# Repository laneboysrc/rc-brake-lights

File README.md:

# RC Brake & Reversing Light controller

This project is an easy-to-build light controller for Radio Controlled cars that simulates realistic brake and reversing lights.

It hooks between your ESC and receiver.

The brake lights automatically turn on for a short, random time when the throttle goes to neutral. The reversing lights turn on when driving backwards.

The light controller supports various ESC modes to ensure the lights are in sync with the way your ESC controls the drive motor.

The aim of the project is to make it easy to build anyone with minimal electronics knowledge. **If you are unable to build it yourself please contact [laneboysrc@gmail.com](mailto:laneboysrc@gmail.com); we'd be happy to sell you one.**

If you are looking for more than just brake lights check out our full-featured [DIY RC Light Controller](https://github.com/laneboysrc/rc-light-controller).

## Building the electronics

The core of the light controller is the inexpensive STC STC15W104. It is a modern interpretation of the venerable 8051 MCU. This MCU was chosen due to its very low cost and because it can be programmed with an inexpensive USB-to-serial adapter, or using the serial port on a Raspberry Pi.

You can find the STC15W104 usually on eBay, AliExpress, Electrodragon, LCSC ...

Beside the MCU you need 3 resistors, a diode and a capacitor. The complete [list of components](electronics/BOM%20-%20Bill%20of%20Materials.txt) can be found in the `electronics/` folder

For convenience the [schematics are available as PDF file](electronics/rc-brake-lights-schematics.pdf).

Due to the small number of required components, the light controller can be easily built on a perfboard. The following image shows how to wire everything up:

(The [Fritzing](http://fritzing.org) source file for this drawing is provided in the `fritzing/` folder)

If you plan to build several controllers it may be worth-while to order printed circuit boards. [Gerber files](gerber-rc-brake-lights.zip) for manufacturing PCBS are provided, as well as the [KiCad source files](electronics/). Note that the PCB uses SMD components rather than through-hole. Still, it is designed for hand-soldering.

## Loading the firmware

You can find the pre-compiled firmware released as part of the project.

If you want to build or modify the firmware you will need [SDCC](http://sdcc.sourceforge.net) and [GNU Make](https://www.gnu.org/software/make/).

To flash the firmware into the STC15W104, use [STCGAL](https://github.com/grigorig/stcgal).

### Loading the firmware with an USB-to-serial adapter

Follow the instructions at [https://github.com/grigorig/stcgal#installation](https://github.com/grigorig/stcgal#installation) to install STCGAL. This programming tool for the STC MCU requires [Python 3](https://www.python.org/downloads/), and the Python 3 libraries `pyserial` and `tqdm`.

- Go to https://www.python.org and download Python; install it.
- Open a Command prompt (run cmd.exe)
- In the command prompt execute `pip install pyserial tqdm`

Connect your USB-to-serial adapter to the RC-brake-lights controller as follows:

Do not connect `+` yet, only after starting STCGAL.

Download the [firmware Intel-HEX file](rc-brake-lights.ihx) and execute STCGAL as follows:

    python stcgal.py -t 12000 --option low_voltage_reset=true --option low_voltage_threshold=0 --option eeprom_lvd_inhibit=true -b 1200 -p COM7 rc-brake-lights.ihx

*Important*: Replace the COM port number with the one of your USB-to-serial adapter. In Windows consult the Device Manager to find out which port number to use.

Once started, STCGAL prompts you to power-cycle the circuit. Plug in `+` and STCGAL should find the MCU and program it. Your controller is now ready to use.

### Loading the firmware using a Raspberry Pi

The Raspberry Pi has a serial port accessible on its GPIO pin-header, so we can use it directly for programming.

Connect the RC-brake-lights controller as follows:

Do not connect `+` yet, only after starting STCGAL.

Download and unpack STCGAL:

    wget https://github.com/grigorig/stcgal/archive/master.zip
    unzip master.zip

Install the required Python 3 modules:

    sudo apt install python3-serial python3-tqdm

Use `sudo raspi-config` and go to `Interface Options`, then `P6 Serial` where you can disable log-in via the serial console, and enable the serial hardware:

    Would you like a login shell to be accessible over serial? Select NO
    Would you like the serial port hardware to be enabled? Select YES

After rebooting, download the [firmware Intel-HEX file](rc-brake-lights.ihx) and execute STCGAL as follows:

    python3 stcgal-master/stcgal.py -p /dev/ttyAMA0 -t 12000 --option low_voltage_reset=true --option low_voltage_threshold=0 --option eeprom_lvd_inhibit=true -b 1200 rc-brake-lights.ihx

Once started, STCGAL prompts you to power-cycle the MCU. Plug in `+` and STCGAL should find the MCU and program it. Your controller is now ready to use.

## Connecting the light controller to your RC system

The light controller has two parallel connectors on the input side. Connect your ESC to one of the plugs and connect the TH input of the receiver with a male-to-male servo cable  to the other plug.

The `B` output drives two red LEDs in parallel for the brake light function, the `R` output drives two white LEDs in parallel for the reversing light function.

## Forward/Reverse setup

Depending on your RC system, out of the box the light controller may operate in the wrong direction (forward and backward reversed). To change this, press and hold the setup button on the light controller for 3 seconds. The LEDs will start flashing quickly.

Now move the throttle on the transmitter to the driving direction that would make the car move `forward`. When LEDs will go out and the light controller has now learned the correct direction of the throttle signal for `forward`. This setting is preserved, so you only have to do this once.

## Changing the ESC mode

When it comes to brake function, ESC models behave differently. The light controller can be programmed for the specific behavior of your ESC.

To change the ESC mode, perform the following steps:
Press and hold the setup button on the light controller. After 3 seconds, the LEDs will start to flash quickly. Press the setup button one more time. The light controller enters the ESC mode setting and flashes the current ESC mode number:

##### 1 flash: Forward/Brake/Reverse with timeout
When driving forward and then immediately pushing the throttle to reverse, the ESC performs a brake function. The ESC only allows driving backwards if the ESC has remained in neutral position for a few seconds.

Example: The China 320A ESC, HPI SC-15WP

##### 2 flashes: Forward/Brake/Reverse
After going forward and then into reverse, the ESC always performs the brake function -- even if the throttle remained in neutral for a long time.

Example: Tamiya ESCs

##### 3 flashes: Forward/Reverse (Crawler mode)
Crawler ESC with drag brake, where the ESC switches from forward directly
into reverse.

##### 4 flashes: Forward/Brake
ESC in race mode where reversing is not allowed.

Press the setup button repeatedly until the desired ESC mode has been selected. Then press-and hold the setup button until the LEDs stop flashing. The ESC mode has now been persistently stored.

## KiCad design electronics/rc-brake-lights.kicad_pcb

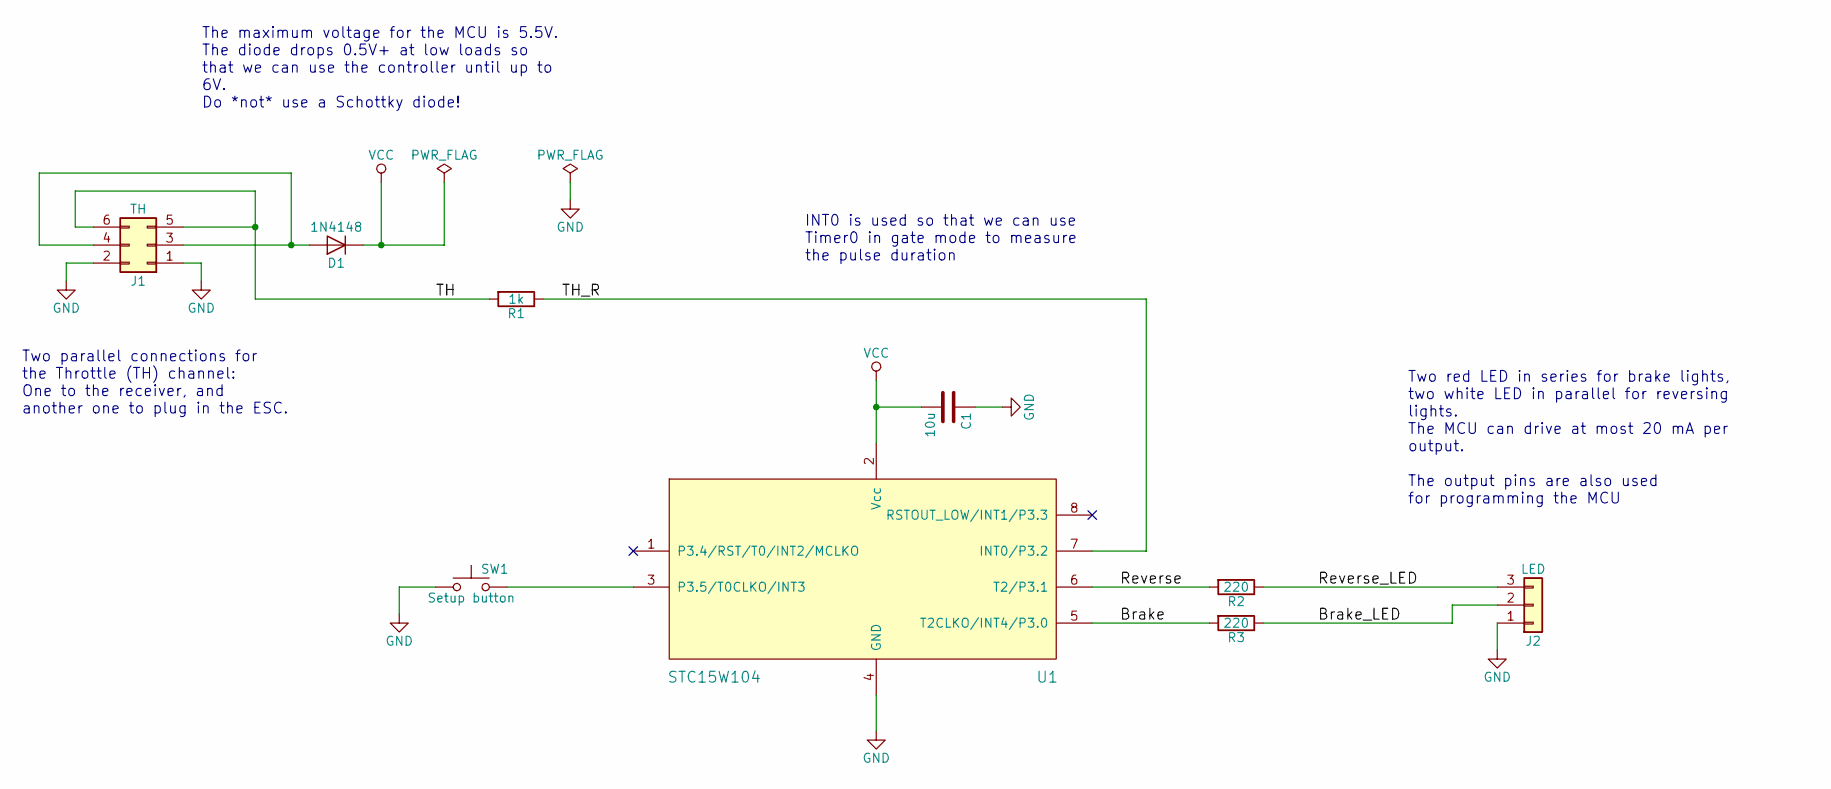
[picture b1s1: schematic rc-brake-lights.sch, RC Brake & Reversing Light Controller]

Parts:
C1: 10u; C_0603_HandSoldering
D1: 1N4148; D_SOD-323_HandSoldering
J1: TH; Pin_header_02x03_board_edge
J2: LED; Pin_Header_Angled_1x03_Pitch2.54mm
R1: 1k; R_0603_HandSoldering
R2, R3: 220; R_0603_HandSoldering
SW1: Setup button; Tact_switch_SMD_6x3_6x2_5
U1: STC15W104; SOIC-8-N

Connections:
/Brake: R3.2, U1.5 (T2CLKO/INT4/P3.0)
/Brake_LED: J2.2, R3.1
/Reverse: R2.2, U1.6 (T2/P3.1)
/Reverse_LED: J2.3, R2.1
/TH: J1.5, J1.6, R1.2
/TH_R: R1.1, U1.7 (INT0/P3.2)
GND: C1.1, J1.1, J1.2, J2.1, SW1.1, U1.4 (GND)
unnamed: D1.2 (A), J1.3, J1.4
unnamed: SW1.2, U1.3 (P3.5/T0CLKO/INT3)
VCC: C1.2, D1.1 (K), U1.2 (Vcc)

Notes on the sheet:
Two parallel connections for the Throttle (TH) channel: One to the receiver, and another one to plug in the ESC.
Two red LED in series for brake lights, two white LED in parallel for reversing lights. The MCU can drive at most 20 mA per output. The output pins are also used for programming the MCU
The maximum voltage for the MCU is 5.5V. The diode drops 0.5V+ at low loads so that we can use the controller until up to 6V. Do *not* use a Schottky diode!
INT0 is used so that we can use Timer0 in gate mode to measure the pulse duration

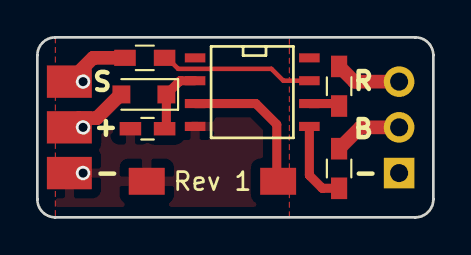
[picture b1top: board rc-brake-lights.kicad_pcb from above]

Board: 2 copper layers, 22.0 x 10.0 mm, 9 parts (1 on the bottom side), 10 nets.

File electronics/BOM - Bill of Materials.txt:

Partlist for the RC Brake & Reversing Light Controller


Perfboard version with through-hole components
----------------------------------------------

Part  Value      Device            Package           Description
C1    10uF/10V   C-Pol             Radial            Electrolytic capacitor, exact value not important
D1    1N4148     D                 Throughole        Signal diode, must be an ordinary silicon diode, not a Schottky diode
J1               Pin-header        2x3               Pin header for throttle servo input
J2               Pin-header        1x3               Pin header for LED output
R1    1k         R                 Throughhole       Resistor 1/8W or more
R2    220        R                 Throughhole       Resistor 1/8W or more
R2    220        R                 Throughhole       Resistor 1/8W or more
U1    STC15W104  MCU               DIP8              STC Microcontroller, 8051-based, 2.5..5.5V supply range
SW1              SPST                                Push button


PCB version with SMD components
-------------------------------

Part  Value      Device            Package           Description
C1    10uF/10V   C0603             0603              MLCC capacitor X7R or X5R
D1    T4         D                 SOD-123           Signal diode marked T4 (eBay, AliExpress)
J1               Pin-header        2x3               Pin header for throttle servo input
J2               Pin-header        1x3               Pin header for LED output
R1    1k         R                 0603              Resistor
R2    220        R                 0603              Resistor
R2    220        R                 0603              Resistor
U1    STC15W104  MCU               SOP8              STC Microcontroller, 8051-based, 2.5..5.5V supply range
SW1              SPST              3x6x2.5mm         Push button, e.g. https://www.aliexpress.com/item/100pcs-3X6X2-5mm-Tactile-Pus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

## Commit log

2018-03-27 PCB draft
2018-03-28 Add firmware skeleton and sublime project
2018-03-29 Add skeleton for modules
2018-04-01 Move IO pins so we can use T0 to measure pulse width
2018-04-01 Add MIT license
2018-04-01 Basic brake/reverse functionality implemented
2018-04-01 Add setup button
2018-04-01 Remove constant if statements
2018-04-02 Remove utils.h, introduce setup mode (replaces channel reversing)
2018-04-02 Implement setup mode and add overall code improvements
2018-04-02 Round-off the PCB edge
2018-04-02 Code cleanup
2018-04-02 Fix ESC mode description
2018-04-03 Make output connector right-angle
2018-04-04 Add low voltage reset
2018-04-04 Remove BOM file
2018-04-04 Add schematics and Gerbers sent for manufactoring
2018-04-04 Fix filename spelling
2018-04-04 Add Fritzing file
2018-04-05 Add BOM and breadboard drawing
2018-04-05 Add wiring diagram
2018-04-06 Add readme
2018-04-06 Update wiring diagram with ESC
2018-04-15 Set low power threshold for STC15W104
    Before we were using settings for STC15F104
2018-04-15 Add pre-compiled hex file
2018-04-15 Fix email link
2018-04-19 Improve documentation
2018-04-20 Add diagram how to connect to Raspi for flashing
2018-04-22 Add documentation for Raspi flashing after testing it
2018-05-04 Improve documentation of installation, add 3D impage
2018-06-02 Fix serial -> pyserial
2018-06-02 Fix spelling in python link
2018-06-02 Change command line to call python script
2018-06-02 Add port to command line
2022-10-16 Add image that shows how to mod for tail light function
